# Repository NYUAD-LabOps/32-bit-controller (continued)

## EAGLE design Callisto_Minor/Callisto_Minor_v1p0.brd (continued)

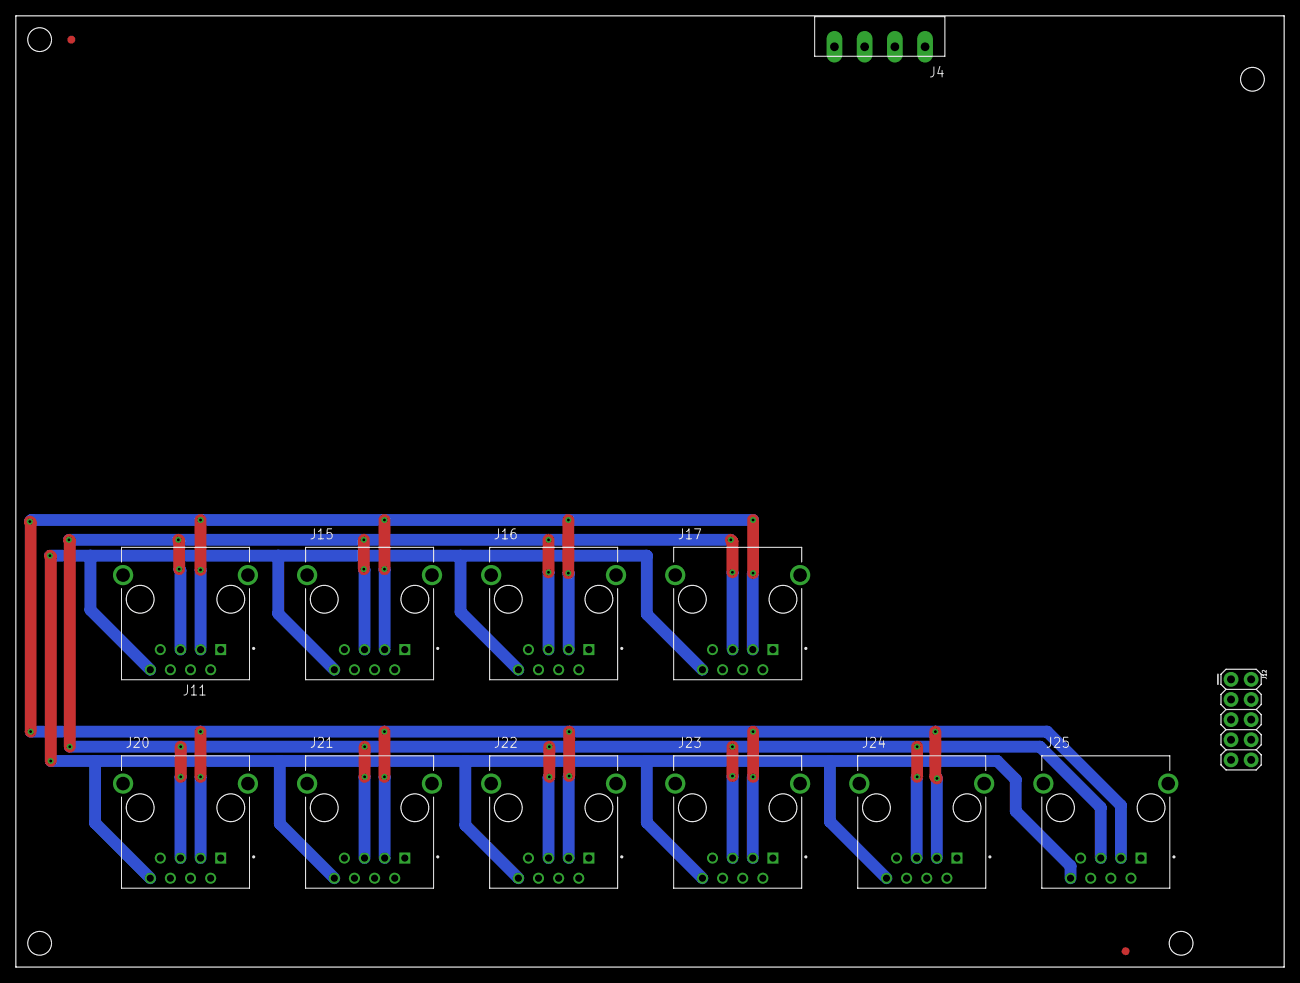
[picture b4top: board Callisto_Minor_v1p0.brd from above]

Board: 2 copper layers, 160.0 x 120.0 mm, 14 parts (0 on the bottom side), 6 nets.

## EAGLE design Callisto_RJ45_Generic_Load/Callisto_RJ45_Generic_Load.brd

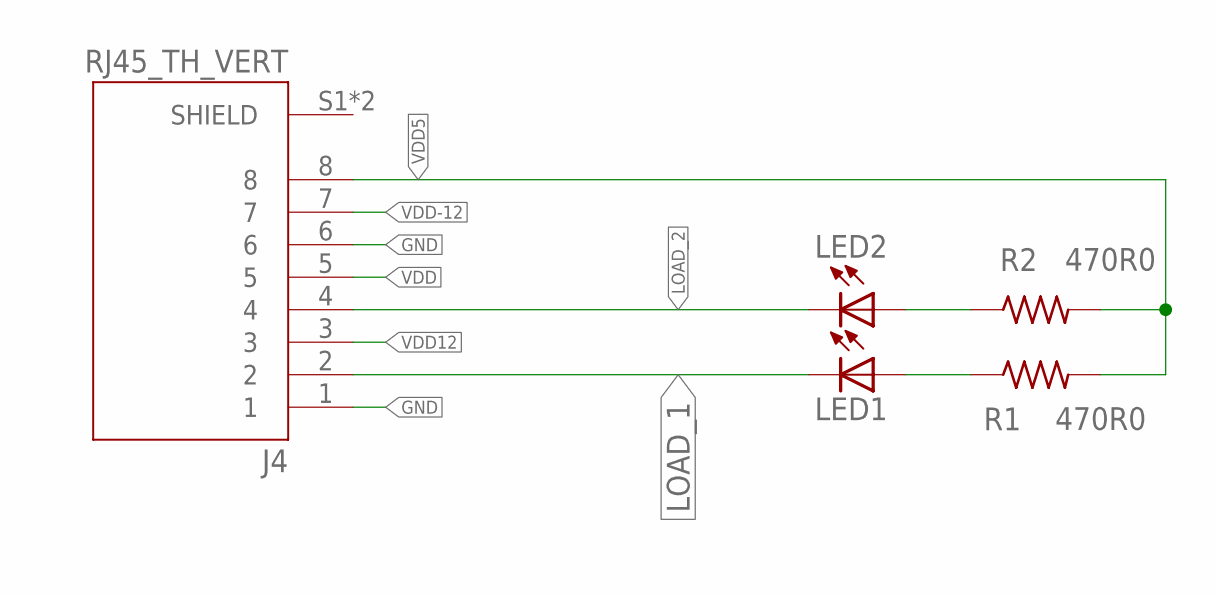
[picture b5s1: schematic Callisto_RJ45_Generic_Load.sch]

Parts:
J4: RJ45_TH_VERT; ASSMANN_A-2014-2S-4-N-R
LED1, LED2: Green; 0805
R1, R2: 470R0; 0402

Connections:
GND: J4.1, J4.6
LOAD_1: J4.2, LED1.2 (C)
LOAD_2: J4.4, LED2.2 (C)
unnamed: LED2.1 (A), R2.P$1 (1)
unnamed: LED1.1 (A), R1.P$1 (1)
VDD: J4.5
VDD5: J4.8, R1.P$2 (2), R2.P$2 (2)
VDD12: J4.3
VDD-12: J4.7

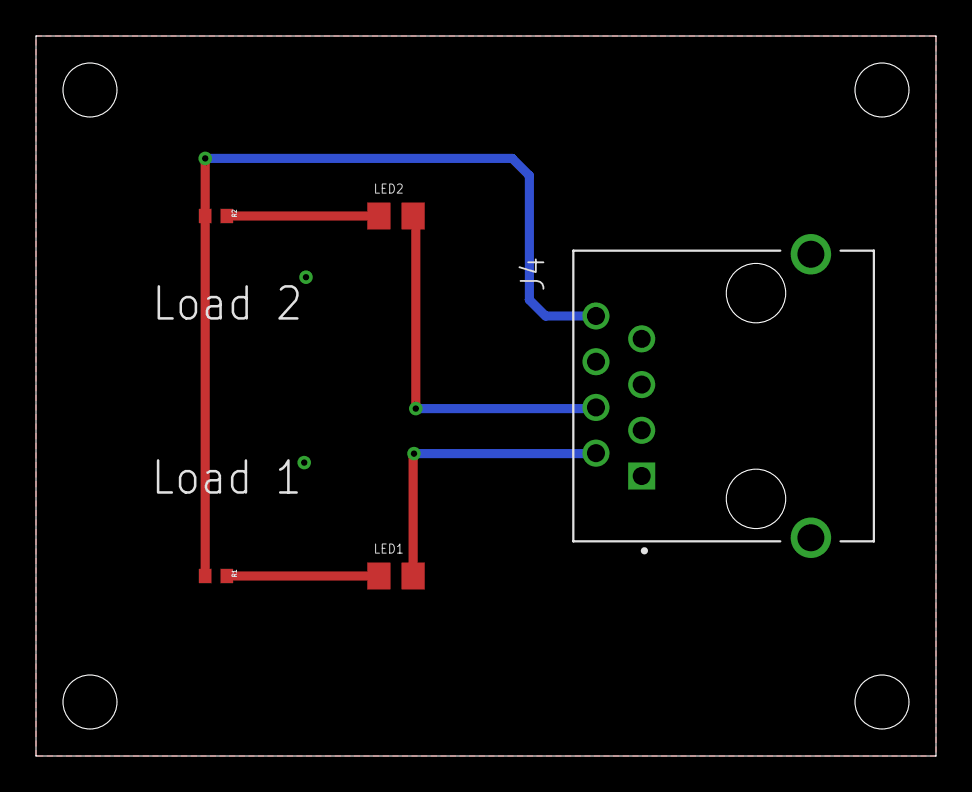
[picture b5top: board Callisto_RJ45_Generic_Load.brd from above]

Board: 2 copper layers, 50.0 x 40.0 mm, 5 parts (0 on the bottom side), 6 nets.

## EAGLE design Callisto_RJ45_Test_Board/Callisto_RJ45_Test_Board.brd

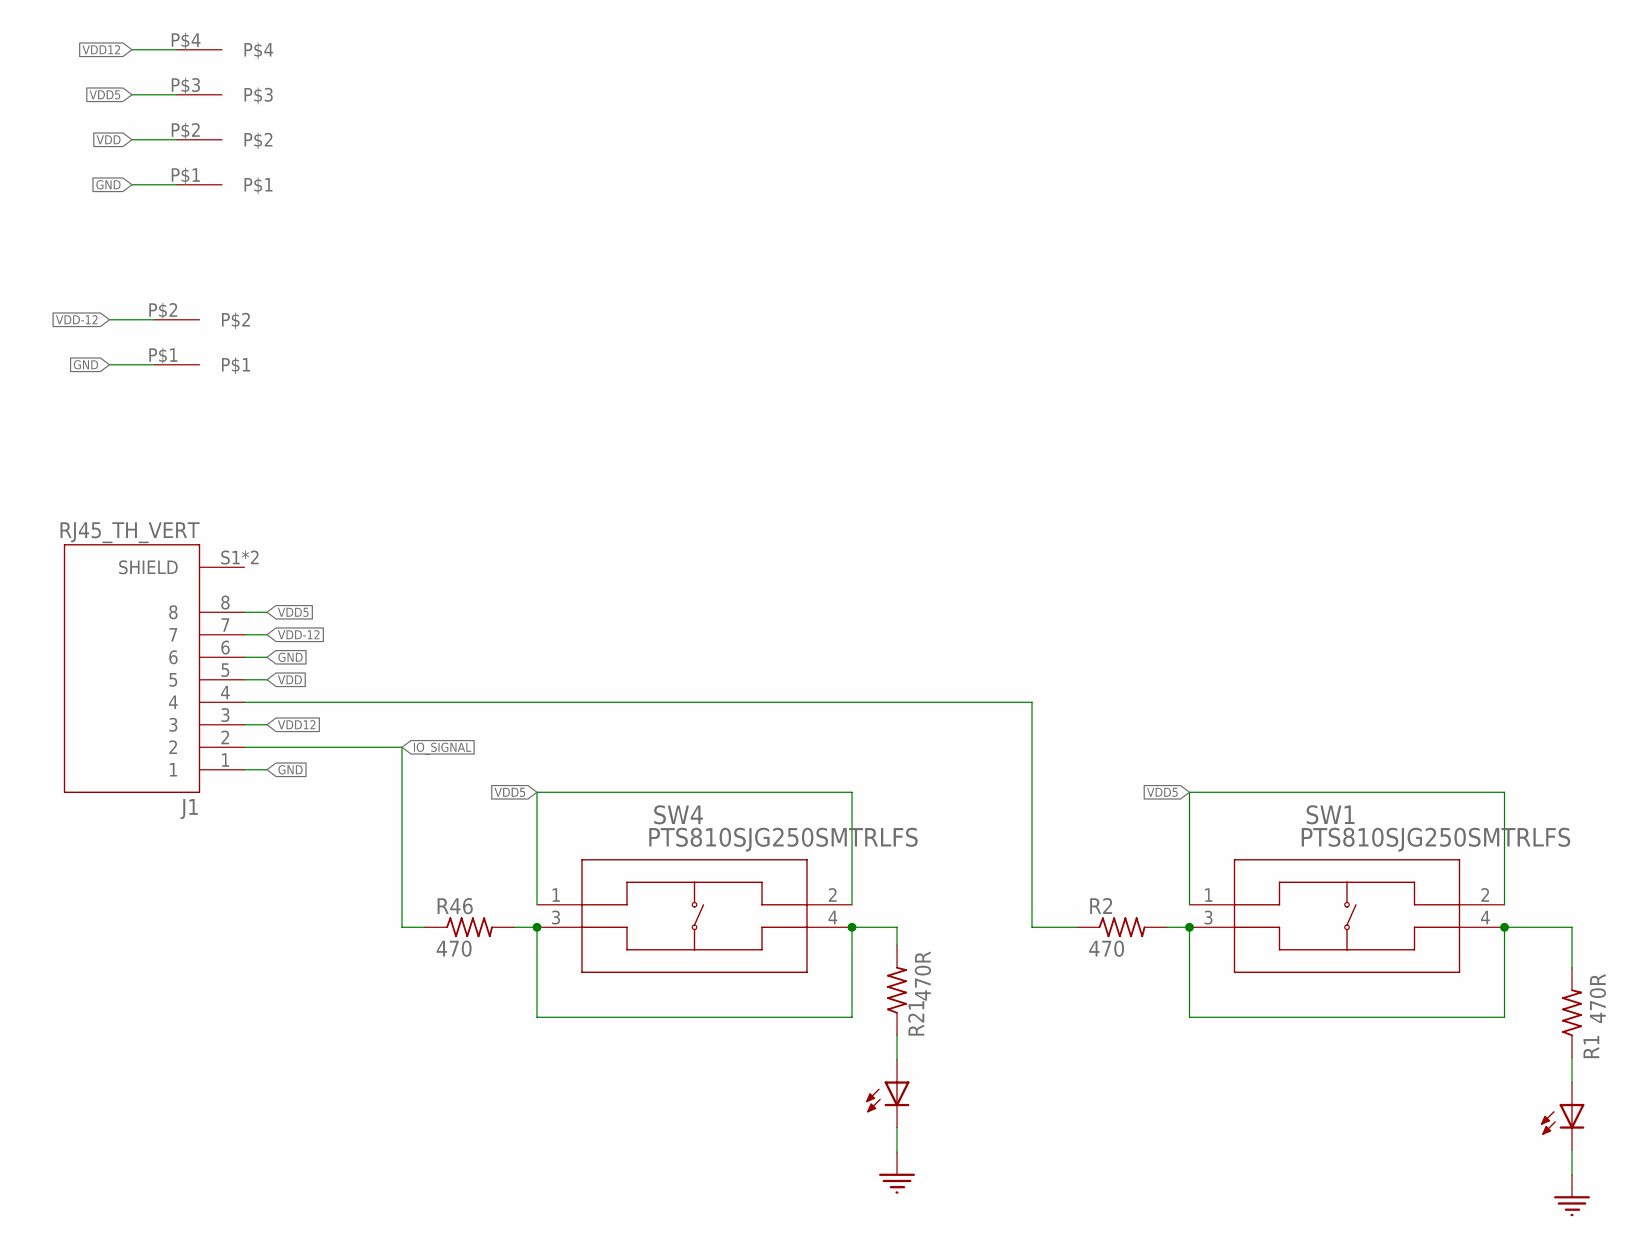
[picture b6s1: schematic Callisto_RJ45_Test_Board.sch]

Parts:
J1: RJ45_TH_VERT; ASSMANN_A-2014-2S-4-N-R
J4: 4-pos; 1X4_3.81MM_PITCH
J11: 2-pos; 2_3.81MM_PITCH
LED1, LED21: Green; 0805
R1, R21: 470R; 0402
R2, R46: 470; 0402
SW1, SW4: PTS810SJG250SMTRLFS; PTS810

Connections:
GND: J1.1, J1.6, J4.P$1, J11.P$1, LED1.2 (C), LED21.2 (C)
IO_SIGNAL: J1.2, R46.P$1 (1)
unnamed: LED1.1 (A), R1.P$1 (1)
unnamed: R1.P$2 (2), R2.P$2 (2), SW1.3, SW1.4
unnamed: J1.4, R2.P$1 (1)
unnamed: LED21.1 (A), R21.P$1 (1)
unnamed: R21.P$2 (2), R46.P$2 (2), SW4.3, SW4.4
VDD: J1.5, J4.P$2
VDD5: J1.8, J4.P$3, SW1.1, SW1.2, SW4.1, SW4.2
VDD12: J1.3, J4.P$4
VDD-12: J1.7, J11.P$2

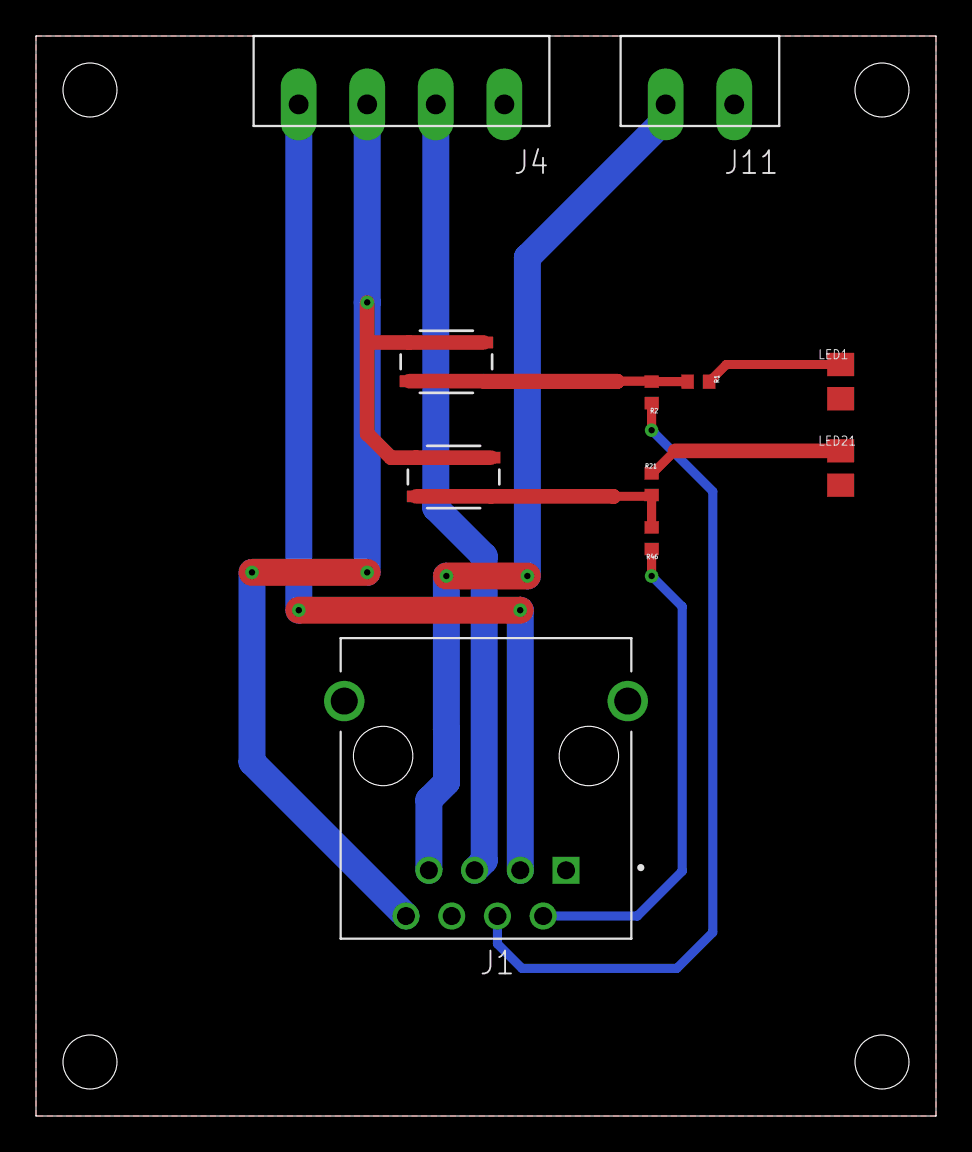
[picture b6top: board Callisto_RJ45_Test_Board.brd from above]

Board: 2 copper layers, 50.0 x 60.0 mm, 11 parts (0 on the bottom side), 11 nets.
